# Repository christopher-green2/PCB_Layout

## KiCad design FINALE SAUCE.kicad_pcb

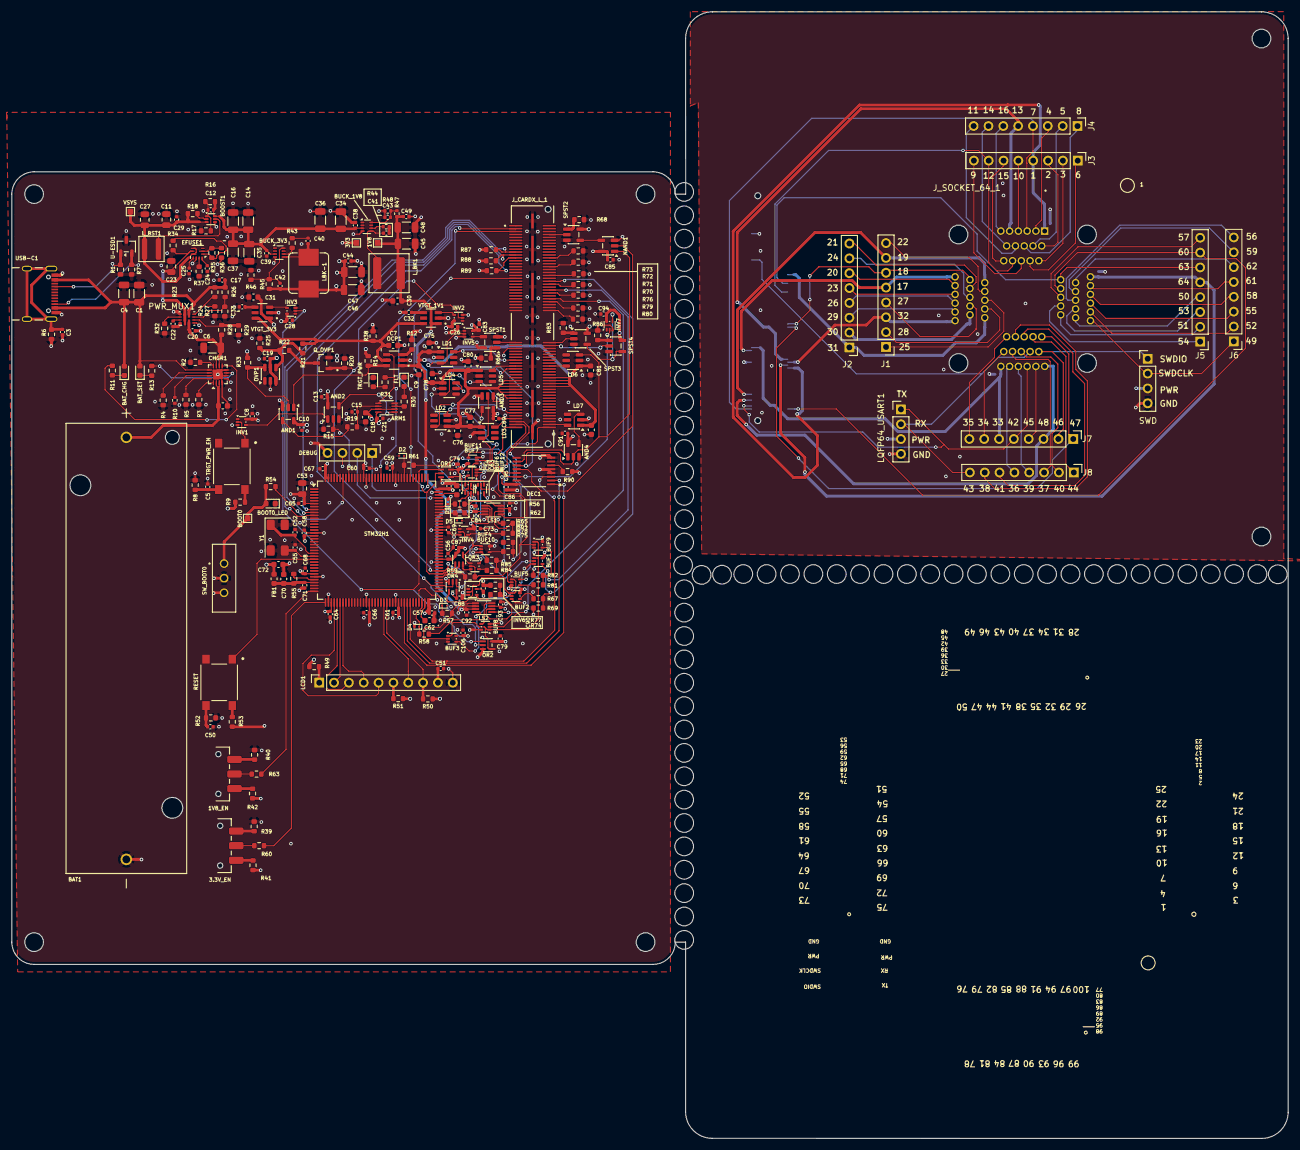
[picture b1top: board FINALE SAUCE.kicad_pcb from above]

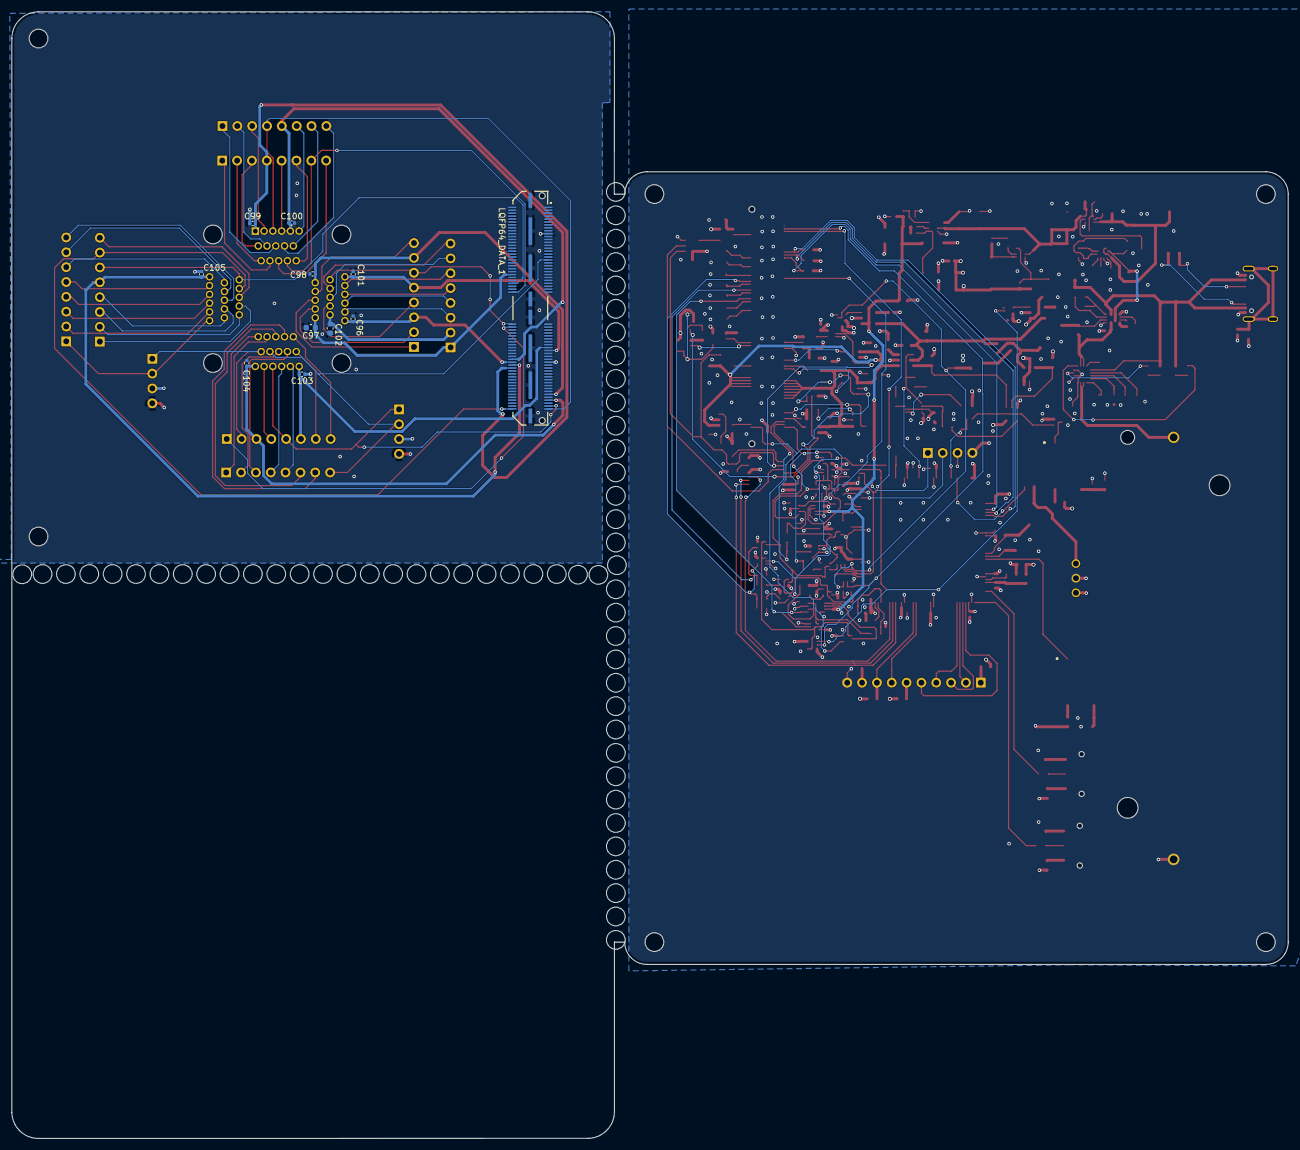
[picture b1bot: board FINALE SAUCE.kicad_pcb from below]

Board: 4 copper layers, 218.4 x 192.8 mm, 352 parts (11 on the bottom side), 236 nets.

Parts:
1V8, 3V3: TestPoint_Flag; TestPoint_Pad_1.0x1.0mm
1V8_EN, 3.3V_EN: JS102011SAQN; SW_SPDT_CK_JS102011SAQN
40, 41, 42, 43, 43#2, 44, 44#2, 45, 45#2, 46, 46#2, 47, 47#2, 48, 48#2, 49, 49#2, 50, 50#2, 51, 51#2, 52, 52#2, 53, 53#2, 54, 54#2, 55, 55#2, 56, 56#2, 57, 57#2, 58, 58#2, 59, 59#2, 60, 60#2, 61, 61#2, 62, 62#2, 63, 63#2, 64, 64#2, 65, 65#2, 66, 67, 68, 69, 70, 71, 72, 73, 74, 75: (no value)
AND1, AND2, AND3, AND4: SN74LVC1G08DBVT; SOT-23-5
ARM1: SN74LVC1G74DCUR; SOP50P310X90-8N
BAT1: 1043 Holder for 18650; BAT_1043
BAT_CHG: Green LED, V_f = 2.4 V at 20 mA, 0603; LED_0603_1608Metric
BAT_SET: Green LED, V_f = 2.4 V at 20 mA, 0603; LED_0603_1608Metric
BOOST1: TPS61023; SOT-563
BOOT0: TestPoint_Square; TestPoint_Pad_1.0x1.0mm
BOOT0_LED: LED; LED_0603_1608Metric
BUCK_1V8, BUCK_3V3: TPS62933P; SOT-583-8
BUF1, BUF2, BUF3, BUF4, BUF5, BUF6, BUF7, BUF8, BUF9, BUF10, BUF11, BUF12: 74AHC1G125; SOT-553
C1, C34, C35, C36: 10u; C_1206_3216Metric
C2: 4.7u; C_0603_1608Metric
C3, C39, C40, C44, C51, C54, C56, C57, C58, C59, C60, C61, C64, C65, C66, C67, C68, C69, C71, C92, C93, C95: 100nF; C_0402_1005Metric
C4, C46, C47: 22uF; C_1206_3216Metric
C5, C8, C26, C28, C50, C73, C74, C79, C83, C84, C85, C86, C87, C88, C89, C90, C91, C94, C106: .1uF; C_0402_1005Metric
C6, C14, C16, C45, C48: 22u; C_1206_3216Metric
C7, C9, C18, C30, C31: 1u; C_0603_1608Metric
C10, C13, C15, C17, C20, C21, C22, C29, C38, C41, C49: 100n; C_0402_1005Metric
C11, C23: 10u; C_0805_2012Metric
C12: 22p; C_0402_1005Metric
C19: 0.1u; C_0402_1005Metric
C24: 2.2n; C_0402_1005Metric
C25: 3.3n; C_0402_1005Metric
C27: 4.7u; C_0805_2012Metric
C32, C33: 1000pf; C_0402_1005Metric
C37: 10uF; C_1206_3216Metric
C42: 75pF; C_0402_1005Metric
C43: 10p; C_0402_1005Metric
C52, C55: 10pF; C_0402_1005Metric
C53: 4.7uF; C_0805_2012Metric
C62, C63: 2.2uF; C_0603_1608Metric
C70, C72, C75, C76, C77, C78, C80, C81, C82: 1uF; C_0603_1608Metric
C96, C98, C99, C100, C101, C103, C104, C105: .1u; C_0402_1005Metric
C97, C102: 2.2u; C_0603_1608Metric
CHGR1: BQ24074; VQFN-16-1EP_3x3mm_P0.5mm_EP1.6x1.6mm
D1, D2, D3, D4, D5: ESD9X5.0ST5G; D_SOD-923
DEC1: 74LCV138; TSSOP16B_TOS
EFUSE1: TPS259470L; Texas_RPU0010A_VQFN-HR-10_2x2mm_P0.5mm
FB1: 220; L_0603_1608Metric
FLT: Red LED, V_f ~ 2.0 V typ, 0603; LED_0603_1608Metric
INV1, INV2, INV3, INV4, INV5, INV6, INV7: 74LVC1GU04DRLR; SOT-553
J1, J2, J3, J4, J5, J6, J7, J8: Conn_01x08_Pin; PinHeader_1x08_P2.54mm_Vertical
J_CARDX_L_1: QSH-060-01-X-D-A; SAMTEC_QSH-060-01-X-D-A
J_SOCKET_64_1: IC51-0644-807; YAMAICHI_IC51-0644-807
LBK-1: 4.7u; L_Bourns_SRP7028A_7.3x6.6mm
LCD1: 358; PinSocket_1x10_P2.54mm_Vertical
LD1, LD2, LD3, LD4, LD5, LD6, LD7: TPS22917LDBVR; SOT-23-6
LQFP64_DATA_1: QTH-060-01-X-D-A; SAMTEC_QTH-060-01-X-D-A
LQFP64_USART1: Conn_01x04_Pin; PinHeader_1x04_P2.54mm_Vertical
LS1, LS2: TXS0102DCUR; VSSOP-8_2.3x2mm_P0.5mm
L_BK1: 6.8u WE-XHMI_6060; L_Wuerth_XHMI-6060
L_BST1: 1uH; L_Wuerth_MAPI-4030
NAND1: SN74LVC1G08DBVT; SOT-23-5
OCP1: MAX4995BAUT_T; SOT95P280X145-6N
OR1, OR2, OR3, OR4: 74AHC1G32QSE-7; SOT-353_SC-70-5
OVP1: TPS3700DDCR; SOT-23-6
PWR_MUX1: TPS2121RUXR; RUX0012A
Q_OVP1: 2N7002
R1, R7: 5.1k; R_0603_1608Metric
R2: 1.18k; R_0603_1608Metric
R3, R8, R9, R14, R19, R38, R39, R40, R41, R42, R46, R50, R51, R52, R53, R54, R64, R66, R67, R68, R70, R71, R72, R73, R74, R75, R76, R79, R80, R81, R83, R84, R86, R90: 10k; R_0603_1608Metric
R4: 46.4k; R_0603_1608Metric
R5: 1.13k; R_0603_1608Metric
R6, R21: 1M; R_0603_1608Metric
R10: 4.12k; R_0402_1005Metric
R11, R13: 330; R_0603_1608Metric
R12: 94.2k; R_0603_1608Metric
R15, R17, R18, R20, R33, R87, R88, R89: 100k; R_0603_1608Metric
R16: 732k; R_0603_1608Metric
R22: 249k; R_0603_1608Metric
R23: 10.2k; R_0603_1608Metric
R24, R27, R29: 5k; R_0603_1608Metric
R25: 258k; R_0603_1608Metric
R26: 21k; R_0603_1608Metric
R28: 18.6k; R_0603_1608Metric
R30: 680; R_0603_1608Metric
R31: 470; R_0603_1608Metric
R32: 44.2k; R_0603_1608Metric
R34: 470k; R_0603_1608Metric
R35: 66.5k; R_0603_1608Metric
R36: 133k; R_0603_1608Metric
R37: 1.10k; R_0603_1608Metric
R43: 3.3; R_0603_1608Metric
R44: 3.3; R_0402_1005Metric
R45: 31.25k; R_0603_1608Metric
R47: 12.5k; R_0402_1005Metric
R48: 10k; R_0402_1005Metric
R49: 220; R_0603_1608Metric
R55: 47; R_0603_1608Metric
R56, R57, R58, R62: 22; R_0603_1608Metric
R59, R60, R61, R63: 100; R_0603_1608Metric
R65, R69, R77, R78, R82, R85: 12k; R_0603_1608Metric
RESET: PTS645; SWITCH_43SMTR92LFS
SPST1, SPST2, SPST3, SPST4: TS5A3166DBVR; SOT-23-5
STM32H1: STM32H753ZIT6; LQFP-144_20x20mm_P0.5mm
SWD: Conn_01x04_Pin; PinHeader_1x04_P2.54mm_Vertical
SW_BOOT0: EG1218; SW_EG1218
TRGT_PWR: Green LED, V_f = 2.4 V at 20 mA, 0603; LED_0603_1608Metric
TRGT_PWR_EN: PTS645; SWITCH_43SMTR92LFS
U-ESD1: TPD2E009DRTR; SOT-23-3
USB-C1: USB4105-GF-A; GCT_USB4105-GF-A
VSYS: TestPoint_Flag; TestPoint_Pad_1.0x1.0mm
VTGT_1V1, VTGT_3V3: TPS22918DBVR; SOT95P280X145-6N
Y1: Crystal_GND24; Crystal_SMD_0603-4Pin_6.0x3.5mm
cg-SWD_Breakout_Parent1: Conn_01x04_Pin; PinHeader_1x04_P2.54mm_Vertical

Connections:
1V8: 1V8.1 (1_1), C30.1, C45.1, C48.1, C49.1, C84.1, C92.1, LS1.3 (VCCA), LS2.3 (VCCA), L_BK1.2, R47.1, VTGT_1V1.1 (VIN)
1V8_ENABLE: INV2.2, OR3.1, OR4.1, Q_OVP1.1, R20.1, STM32H1.80 (PD11)
3V3: 3V3.1 (1_1), AND1.5 (VCC), AND2.5 (VCC), AND3.5 (VCC), AND4.5 (VCC), ARM1.2 (D), ARM1.7 (~PRE), ARM1.8 (VCC), BUF1.5 (VCC), BUF2.5 (VCC), BUF3.5 (VCC), BUF4.5 (VCC), BUF5.5 (VCC), BUF6.5 (VCC), BUF7.5 (VCC), BUF8.5 (VCC), BUF9.5 (VCC), BUF10.5 (VCC), BUF11.5 (VCC), BUF12.5 (VCC), C8.1, C10.1, C13.2, C18.1, C19.1, C21.1, C26.1, C28.1, C31.1, C42.1, C44.1, C46.1, C47.1, C51.1, C53.1, C54.1, C56.1, C57.1, C58.1, C59.1, C60.1, C61.1, C64.1, C65.1, C66.1, C67.1, C68.1, C72.1, C73.1, C74.1, C79.1, C83.1, C85.1, C86.1, C87.1, C88.1, C89.1, C90.1, C91.1, C93.1, C94.1, C95.1, C106.1, CHGR1.5 (EN2), DEC1.16 (VCC), FB1.1, INV1.5 (VCC), INV2.5 (VCC), INV3.5 (VCC), INV4.5 (VCC), INV5.5 (VCC), INV6.5 (VCC), INV7.5 (VCC), J_CARDX_L_1.65, LBK-1.2, LCD1.9 (VCC), LS1.7 (VCCB), LS2.7 (VCCB), NAND1.5 (VCC), OR1.5 (VCC), OR2.5 (VCC), OR3.5 (VCC), OR4.5 (VCC), OVP1.3 (INA+), OVP1.5 (VDD), R9.2, R14.1, R33.1, R41.1, R42.2, R45.1, R49.1, R50.1, R51.1, R53.2, R87.1, R88.1, R89.1, R90.1, SPST1.5 (V+), SPST2.5 (V+), SPST3.5 (V+), SPST4.5 (V+), STM32H1.6 (VBAT), STM32H1.17 (VDD), STM32H1.30 (VDD), STM32H1.39 (VDD), STM32H1.52 (VDD), STM32H1.62 (VDD), STM32H1.72 (VDD), STM32H1.84 (VDD), STM32H1.108 (VDD), STM32H1.121 (VDD), STM32H1.131 (VDD), STM32H1.143 (PDR_ON), STM32H1.144 (VDD), SW_BOOT0.3, VTGT_3V3.1 (VIN), cg-SWD_Breakout_Parent1.3
3V3_ENABLE: INV3.2, OR1.1, OR2.1, STM32H1.112 (PC11)
5V: BOOST1.6 (VOUT), BUCK_1V8.3 (VIN), BUCK_3V3.3 (VIN), C12.1, C14.1, C16.1, C34.1, C35.1, C36.1, C37.1, C38.1, C39.1, R16.1
/Parent_MCU/HSE_IN: C52.1, STM32H1.23 (PH0), Y1.1
/Parent_MCU/HSE_OUT: C55.1, STM32H1.24 (PH1), Y1.3
/Parent_MCU/LCD_DATA/COMMAND: LCD1.7 (D/C), STM32H1.57 (PG1)
/Parent_MCU/LCD_NRST: LCD1.8 (RESET), R50.2, STM32H1.58 (PE7)
/Parent_MCU/SPI_MISO: LCD1.2 (MISO), STM32H1.42 (PA6)
/Parent_MCU/SPI_MOSI: LCD1.4 (MOSI), STM32H1.43 (PA7)
/Parent_MCU/SPI_NSS: LCD1.5 (TFT_CS), STM32H1.40 (PA4)
/Parent_MCU/SPI_SCK: LCD1.3 (SCK), STM32H1.41 (PA5)
/Parent_MCU/SWDCLK: STM32H1.105 (PA13), cg-SWD_Breakout_Parent1.2
/Parent_MCU/SWDIO: STM32H1.109 (PA14), cg-SWD_Breakout_Parent1.1
/Parent_MCU/VDDA: C70.1, C71.1, FB1.2, R55.1, STM32H1.33 (VDDA)
/PowerSupply/EFUSE_DVDT: C25.1, EFUSE1.7 (dVdt)
/PowerSupply/ILIM_NODE: CHGR1.12 (ILIM), R2.2
/PowerSupply/ISET_NODE: CHGR1.16 (ISET), R5.2
/PowerSupply/TMR_NODE: CHGR1.14 (TMR), R4.2
/PowerSupply/USB_CC1: R1.2, U-ESD1.1 (D+), USB-C1.A5 (CC1)
/PowerSupply/USB_CC2: R7.2, U-ESD1.2 (D-), USB-C1.B5 (CC2)
/PowerSupply/VSYS_ILM: PWR_MUX1.10 (ILIM), R32.2
/PowerSupply/VSYS_OV1: PWR_MUX1.5 (OV1), R26.1, R27.2
/PowerSupply/VSYS_OV2: PWR_MUX1.4 (OV2), R28.1, R29.2
/PowerSupply/VSYS_PR1: PWR_MUX1.6 (PR1), R23.1, R24.2
/PowerSupply/VSYS_SS: C22.1, PWR_MUX1.11 (SS)
/Profile_Switching/64_1: C99.1, J3.4, J_SOCKET_64_1.1, LQFP64_DATA_1.92
/Profile_Switching/64_2: J3.3, J_SOCKET_64_1.2
/Profile_Switching/64_3: J3.2, J_SOCKET_64_1.3
/Profile_Switching/64_4: J4.3, J_SOCKET_64_1.4
/Profile_Switching/64_5: J4.2, J_SOCKET_64_1.5
/Profile_Switching/64_6: J3.1, J_SOCKET_64_1.6
/Profile_Switching/64_7: J4.4, J_SOCKET_64_1.7, LQFP64_DATA_1.119
/Profile_Switching/64_8: J4.1, J_SOCKET_64_1.8
/Profile_Switching/64_9: J3.8, J_SOCKET_64_1.9
/Profile_Switching/64_10: J3.5, J_SOCKET_64_1.10
/Profile_Switching/64_11: J4.8, J_SOCKET_64_1.11
/Profile_Switching/64_12: J3.7, J_SOCKET_64_1.12, LQFP64_DATA_1.60
/Profile_Switching/64_13: C100.1, J4.5, J_SOCKET_64_1.13, LQFP64_DATA_1.86
/Profile_Switching/64_14: J4.7, J_SOCKET_64_1.14
/Profile_Switching/64_15: J3.6, J_SOCKET_64_1.15
/Profile_Switching/64_16: J4.6, J_SOCKET_64_1.16
/Profile_Switching/64_17: C101.1, J1.5, J_SOCKET_64_1.17, LQFP64_DATA_1.79
/Profile_Switching/64_18: J1.6, J_SOCKET_64_1.18, LQFP64_DATA_1.62
/Profile_Switching/64_19: C98.1, J1.7, J_SOCKET_64_1.19, LQFP64_DATA_1.109
/Profile_Switching/64_20: J2.6, J_SOCKET_64_1.20
/Profile_Switching/64_21: J2.8, J_SOCKET_64_1.21
/Profile_Switching/64_22: J1.8, J_SOCKET_64_1.22
/Profile_Switching/64_23: J2.5, J_SOCKET_64_1.23
/Profile_Switching/64_24: J2.7, J_SOCKET_64_1.24
/Profile_Switching/64_25: J1.1, J_SOCKET_64_1.25
/Profile_Switching/64_26: J2.4, J_SOCKET_64_1.26
/Profile_Switching/64_27: J1.4, J_SOCKET_64_1.27
/Profile_Switching/64_28: J1.2, J_SOCKET_64_1.28
/Profile_Switching/64_29: J2.3, J_SOCKET_64_1.29
/Profile_Switching/64_30: C102.1, J2.2, J_SOCKET_64_1.30
/Profile_Switching/64_31: C97.1, J2.1, J_SOCKET_64_1.31, LQFP64_DATA_1.48
/Profile_Switching/64_32: C96.1, J1.3, J_SOCKET_64_1.32, LQFP64_DATA_1.88
/Profile_Switching/64_33: C103.1, J7.6, J_SOCKET_64_1.33, LQFP64_DATA_1.77
/Profile_Switching/64_34: J7.7, J_SOCKET_64_1.34
/Profile_Switching/64_35: J7.8, J_SOCKET_64_1.35
/Profile_Switching/64_36: J8.5, J_SOCKET_64_1.36
/Profile_Switching/64_37: J8.3, J_SOCKET_64_1.37
/Profile_Switching/64_38: J8.7, J_SOCKET_64_1.38
/Profile_Switching/64_39: J8.4, J_SOCKET_64_1.39
/Profile_Switching/64_40: J8.2, J_SOCKET_64_1.40
/Profile_Switching/64_41: J8.6, J_SOCKET_64_1.41
/Profile_Switching/64_42: J7.5, J_SOCKET_64_1.42, LQFP64_DATA_1.117, LQFP64_USART1.1
/Profile_Switching/64_43: J8.8, J_SOCKET_64_1.43, LQFP64_DATA_1.37, LQFP64_USART1.2
/Profile_Switching/64_44: J8.1, J_SOCKET_64_1.44
/Profile_Switching/64_45: J7.4, J_SOCKET_64_1.45
/Profile_Switching/64_46: J7.2, J_SOCKET_64_1.46, SWD.1
/Profile_Switching/64_47: J7.1, J_SOCKET_64_1.47, LQFP64_DATA_1.64
/Profile_Switching/64_48: C104.2, J7.3, J_SOCKET_64_1.48, LQFP64_DATA_1.113
/Profile_Switching/64_49: J6.1, J_SOCKET_64_1.49, SWD.2
/Profile_Switching/64_50: J5.4, J_SOCKET_64_1.50
/Profile_Switching/64_51: J5.2, J_SOCKET_64_1.51
/Profile_Switching/64_52: J6.2, J_SOCKET_64_1.52
/Profile_Switching/64_53: J5.3, J_SOCKET_64_1.53
/Profile_Switching/64_54: J5.1, J_SOCKET_64_1.54
/Profile_Switching/64_55: J6.3, J_SOCKET_64_1.55
/Profile_Switching/64_56: J6.8, J_SOCKET_64_1.56
/Profile_Switching/64_57: J5.8, J_SOCKET_64_1.57
/Profile_Switching/64_58: J6.4, J_SOCKET_64_1.58
/Profile_Switching/64_59: J6.7, J_SOCKET_64_1.59
/Profile_Switching/64_60: J5.7, J_SOCKET_64_1.60, LQFP64_DATA_1.120
/Profile_Switching/64_61: J6.5, J_SOCKET_64_1.61
/Profile_Switching/64_62: J6.6, J_SOCKET_64_1.62
/Profile_Switching/64_63: J5.6, J_SOCKET_64_1.63, LQFP64_DATA_1.54
/Profile_Switching/64_64: C105.1, J5.5, J_SOCKET_64_1.64, LQFP64_DATA_1.90
/Profile_Switching/LQFP64_PIN_7: BUF11.4, J_CARDX_L_1.119, R84.2, R85.1
/Profile_Switching/LQFP64_PIN_12: J_CARDX_L_1.60, R80.2
/Profile_Switching/LQFP64_PIN_17: J_CARDX_L_1.79, LD4.6 (VOUT)
/Profile_Switching/LQFP64_PIN_18: J_CARDX_L_1.62, SPST3.2
/Profile_Switching/LQFP64_PIN_19: J_CARDX_L_1.109, LD2.6 (VOUT)
/Profile_Switching/LQFP64_PIN_31: J_CARDX_L_1.48, R76.2
/Profile_Switching/LQFP64_PIN_33: J_CARDX_L_1.77, LD5.6 (VOUT)
/Profile_Switching/LQFP64_PIN_42: BUF12.2, J_CARDX_L_1.117, LS1.5 (A1)
/Profile_Switching/LQFP64_PIN_43: BUF6.4, J_CARDX_L_1.37, LS1.4 (A2)
/Profile_Switching/LQFP64_PIN_47: J_CARDX_L_1.64, SPST4.2
/Profile_Switching/LQFP64_PIN_48: J_CARDX_L_1.113, LD3.6 (VOUT)
/Profile_Switching/LQFP64_PIN_60: BUF7.4, J_CARDX_L_1.120, R75.2, R78.1
/Profile_Switching/LQFP64_PIN_63: J_CARDX_L_1.54, R79.2
/Profile_Switching/LQFP100_PIN_10: J_CARDX_L_1.61, SPST1.2
/Profile_Switching/LQFP100_PIN_11: J_CARDX_L_1.78, LD6.6 (VOUT)
/Profile_Switching/LQFP100_PIN_14: BUF9.4, J_CARDX_L_1.46, R81.2, R82.1
/Profile_Switching/LQFP100_PIN_19: J_CARDX_L_1.73, LD1.6 (VOUT)
/Profile_Switching/LQFP100_PIN_20: J_CARDX_L_1.24, R73.2
/Profile_Switching/LQFP100_PIN_22: J_CARDX_L_1.118, LD7.6 (VOUT)
/Profile_Switching/LQFP100_PIN_27: J_CARDX_L_1.08, SPST2.2
/Profile_Switching/LQFP100_PIN_49: J_CARDX_L_1.30, R72.2
/Profile_Switching/LQFP100_PIN_68: BUF8.2, J_CARDX_L_1.52, LS2.5 (A1)
/Profile_Switching/LQFP100_PIN_69: BUF3.4, J_CARDX_L_1.115, LS2.4 (A2)
/Profile_Switching/LQFP100_PIN_74: J_CARDX_L_1.36, R71.2
/Profile_Switching/LQFP100_PIN_94: BUF1.4, J_CARDX_L_1.40, R67.2, R69.1
/Profile_Switching/LQFP100_PIN_99: J_CARDX_L_1.42, R70.2
/Profile_Switching/TGT_PWR64: LQFP64_DATA_1.87, LQFP64_USART1.3, SWD.3
CARD_ID0_N: J_CARDX_L_1.19, R87.2, STM32H1.10 (PF0)
CARD_ID1_N: J_CARDX_L_1.21, R88.2, STM32H1.9 (PC15)
CARD_ID2_N: J_CARDX_L_1.23, R89.2, STM32H1.8 (PC14)
GND: AND1.3 (GND), AND2.3 (GND), AND3.3 (GND), AND4.3 (GND), ARM1.4 (GND), BAT1.N, BOOST1.4 (GND), BOOT0_LED.1 (K), BUCK_1V8.4 (GND), BUCK_3V3.4 (GND), BUF1.3 (GND), BUF2.3 (GND), BUF3.3 (GND), BUF4.3 (GND), BUF5.3 (GND), BUF6.3 (GND), BUF7.3 (GND), BUF8.3 (GND), BUF9.3 (GND), BUF10.3 (GND), BUF11.3 (GND), BUF12.3 (GND), C1.2, C2.2, C3.2, C4.2, C5.2, C6.2, C7.2, C8.2, C9.2, C10.2, C11.2, C13.1, C14.2, C15.2, C16.2, C17.2, C18.2, C19.2, C20.2, C21.2, C22.2, C23.2, C24.2, C25.2, C26.2, C27.2, C28.2, C29.2, C30.2, C31.2, C32.2, C33.2, C34.2, C35.2, C36.2, C37.2, C38.2, C39.2, C43.2, C44.2, C45.2, C46.2, C47.2, C48.2, C49.2, C50.2, C51.2, C52.2, C53.2, C54.2, C55.2, C56.2, C57.2, C58.2, C59.2, C60.2, C61.2, C62.2, C63.2, C64.2, C65.2, C66.2, C67.2, C68.2, C69.2, C70.2, C71.2, C72.2, C73.2, C74.2, C75.2, C76.2, C77.2, C78.2, C79.2, C80.2, C81.2, C82.2, C83.2, C84.2, C85.2, C86.2, C87.2, C88.2, C89.2, C90.2, C91.2, C92.2, C93.2, C94.2, C95.2, C106.2, CHGR1.4 (~CE), CHGR1.6 (EN1), CHGR1.8 (VSS), CHGR1.17 (EXP), D1.2 (A), D2.2 (A), D3.2 (A), D4.2 (A), D5.2 (A), DEC1.4 (*G2A), DEC1.5 (*G2B), DEC1.8 (GND), EFUSE1.8 (GND), FLT.1 (K), INV1.3 (GND), INV2.3 (GND), INV3.3 (GND), INV4.3 (GND), INV5.3 (GND), INV6.3 (GND), INV7.3 (GND), J_CARDX_L_1.G1_1 (GND1), J_CARDX_L_1.G1_2 (GND1__1), J_CARDX_L_1.G1_3 (GND1__2), J_CARDX_L_1.G1_4 (GND1__3), J_CARDX_L_1.G2_1 (GND2), J_CARDX_L_1.G2_2 (GND2__1), J_CARDX_L_1.G2_3 (GND2__2), J_CARDX_L_1.G2_4 (GND2__3), LCD1.10 (GND), LD1.2 (GND), LD2.2 (GND), LD3.2 (GND), LD4.2 (GND), LD5.2 (GND), LD6.2 (GND), LD7.2 (GND), LS1.2 (GND), LS2.2 (GND), NAND1.3 (GND), OCP1.2 (GND), OR1.3 (GND), OR2.3 (GND), OR3.3 (GND), OR4.3 (GND), OVP1.2 (GND), PWR_MUX1.3 (CP2), PWR_MUX1.9 (ST), PWR_MUX1.12 (GND), Q_OVP1.2, R1.1, R2.1, R3.1, R4.1, R5.1, R6.1, R7.1, R8.2, R10.1, R12.2, R15.2, R17.2, R20.2, R24.1, R25.2, R27.1, R29.1, R32.1, R36.1, R37.1, R38.2, R39.2, R40.2, R46.2, R48.2, R52.2, R65.1, R66.2, R68.2, R69.2, R70.1, R71.1, R72.1, R73.1, R76.1, R77.1, R78.2, R79.1, R80.1, R82.2, R83.2, R85.2, R86.2, SPST1.3 (GND), SPST2.3 (GND), SPST3.3 (GND), SPST4.3 (GND), STM32H1.16 (VSS), STM32H1.31 (VSSA), STM32H1.38 (VSS), STM32H1.51 (VSS), STM32H1.61 (VSS), STM32H1.83 (VSS), STM32H1.94 (VSS), STM32H1.107 (VSS), STM32H1.120 (VSS), STM32H1.130 (VSS), SW_BOOT0.2, TRGT_PWR.1 (K), U-ESD1.3 (GND), USB-C1.A1_B12 (GND), USB-C1.B1_A12 (GND__1), VTGT_1V1.2 (GND), VTGT_3V3.2 (GND), Y1.2 (G), Y1.4 (G), cg-SWD_Breakout_Parent1.4
GND64: C96.2, C97.2, C98.2, C99.2, C100.2, C101.2, C102.2, C103.2, C104.1, C105.2, LQFP64_DATA_1.19, LQFP64_DATA_1.G1 (GND), LQFP64_DATA_1.G2 (GND__1), LQFP64_DATA_1.G3 (GND__2), LQFP64_DATA_1.G4 (GND__3), LQFP64_DATA_1.G5 (GND__4), LQFP64_DATA_1.G6 (GND__5), LQFP64_DATA_1.G7 (GND__6), LQFP64_DATA_1.G8 (GND__7), LQFP64_USART1.4, SWD.4
LQFP64_1V8_ENABLE: BUF4.1, BUF10.1, INV4.2, OR3.4
LQFP64_3V3_ENABLE: BUF6.1, BUF7.1, BUF11.1, BUF12.1, OR1.4
LQFP64_ENABLE: J_CARDX_L_1.05, OR1.2, OR3.2, STM32H1.79 (PD10)
LQFP100_1V8_ENABLE: BUF2.1, BUF5.1, INV6.2, OR4.4
LQFP100_3V3_ENABLE: BUF1.1, BUF3.1, BUF8.1, BUF9.1, OR2.4
LQFP100_ENABLE: J_CARDX_L_1.03, OR2.2, OR4.2, STM32H1.75 (PB14)
MCU_1V8_FLAG: 1V8_EN.2, R63.2
MCU_3V3_FLAG: 3.3V_EN.2, R60.2
MCU_PROFILE_SEL1: DEC1.1 (A), STM32H1.64 (PE11)
MCU_PROFILE_SEL2: DEC1.2 (B), STM32H1.65 (PE12)
MCU_PROFILE_SEL3: DEC1.3 (C), STM32H1.66 (PE13)
MCU_TARGET_PROFILE_ENABLE: AND2.2 (B), R15.1, STM32H1.136 (PB6)
unnamed: 1V8_EN.1, R40.1
unnamed: 1V8_EN.3, R42.1
unnamed: 3.3V_EN.1, R39.1
unnamed: 3.3V_EN.3, R41.2
unnamed: AND1.4 (Y), R19.1
unnamed: AND2.4 (Y), ARM1.1 (CLK)
unnamed: ARM1.6 (~CLR), C15.1, R19.2
unnamed: ARM1.3 (~Q), R30.1
unnamed: BAT_CHG.1 (K), R11.1
unnamed: BAT_SET.1 (K), R13.1
unnamed: BOOST1.2 (EN), R18.2
unnamed: BOOST1.1 (FB), C12.2, R16.2, R17.1
unnamed: BOOST1.5 (SW), L_BST1.2
unnamed: BOOT0.1 (1_1), BOOT0_LED.2 (A), R54.1, SW_BOOT0.1
unnamed: BUCK_1V8.6 (BST), R44.1
unnamed: BUCK_1V8.8 (FB), C43.1, R47.2, R48.1
unnamed: BUCK_1V8.5 (SW), C41.2, L_BK1.1
unnamed: BUCK_3V3.6 (BST), R43.1
unnamed: BUCK_3V3.8 (FB), C42.2, R45.2, R46.1
unnamed: BUCK_3V3.5 (SW), C40.2, LBK-1.1
unnamed: BUF2.4, R67.1
unnamed: BUF4.4, R75.1
unnamed: BUF5.4, R81.1
unnamed: BUF10.4, R84.1
unnamed: C5.1, R8.1, TRGT_PWR_EN.4
unnamed: C40.1, R43.2
unnamed: C41.1, R44.2
unnamed: C50.1, R52.1, RESET.4
unnamed: C62.1, STM32H1.71 (VCAP)
unnamed: C63.1, STM32H1.106 (VCAP)
unnamed: BAT1.P, C2.1, CHGR1.2 (BAT_2), CHGR1.3 (BAT_3)
unnamed: CHGR1.15 (ITERM), R10.2
unnamed: CHGR1.1 (TS), R3.2
unnamed: CHGR1.9 (~CHG), R11.2
unnamed: CHGR1.7 (~PGOOD), R13.2
unnamed: D1.1 (K), R56.1, STM32H1.102 (PA10)
unnamed: D2.1 (K), R61.1, STM32H1.117 (PD3)
unnamed: D3.1 (K), R57.1, STM32H1.69 (PB10)
unnamed: D4.1 (K), R58.1, STM32H1.70 (PB11)
unnamed: D5.1 (K), R62.1, STM32H1.101 (PA9)
unnamed: DEC1.6 (G1), R90.2
unnamed: EFUSE1.1 (EN_UVLO), R34.1, R35.2
unnamed: EFUSE1.9 (ILM), R37.2
unnamed: C23.1, EFUSE1.5 (IN), PWR_MUX1.1 (OUT), PWR_MUX1.8 (OUT__2), R34.2
unnamed: C24.1, EFUSE1.10 (ITIMER)
unnamed: EFUSE1.2 (OVCSEL), R35.1, R36.2
unnamed: FLT.2 (A), R30.2
unnamed: INV1.2, TRGT_PWR_EN.1
unnamed: INV4.4, R64.1
unnamed: INV5.4, SPST1.4
unnamed: INV6.4, R74.1
unnamed: INV7.4, SPST3.4, SPST4.4
unnamed: LCD1.6 (CARD_CS), R51.2
unnamed: LCD1.1 (LITE), R49.2
unnamed: AND3.4, LD2.3 (~ON)
unnamed: AND4.4, LD7.3 (~ON)
unnamed: LS1.6 (OE), R64.2, R65.2
unnamed: LS2.6 (OE), R74.2, R77.2
unnamed: NAND1.4, SPST2.4
unnamed: OCP1.3 (SETI), R12.1
unnamed: OVP1.4 (INB-), R21.2, R22.1, R25.1
unnamed: Q_OVP1.3, R22.2
unnamed: R9.1, TRGT_PWR_EN.2
unnamed: R53.1, RESET.2
unnamed: R66.1, SPST1.1
unnamed: R68.1, SPST2.1
unnamed: R83.1, SPST3.1
unnamed: R86.1, SPST4.1
unnamed: R54.2, STM32H1.138 (BOOT0)
unnamed: RESET.1, STM32H1.25 (NRST)
unnamed: R63.1, STM32H1.36 (PA2)
unnamed: R60.1, STM32H1.37 (PA3)
unnamed: R59.1, STM32H1.78 (PD9)
unnamed: C69.1, STM32H1.95 (VDD33_USB)
unnamed: R55.2, STM32H1.32 (VREF+)
unnamed: R31.2, TRGT_PWR.2 (A)
unnamed: C3.1, R6.2, USB-C1.SH1 (SHELL_GND), USB-C1.SH2 (SHELL_GND__1), USB-C1.SH3 (SHELL_GND__2), USB-C1.SH4 (SHELL_GND__3)
unnamed: C32.1, VTGT_1V1.4 (CT)
unnamed: INV2.4, VTGT_1V1.3 (ON)
unnamed: C33.1, VTGT_3V3.4 (CT)
unnamed: INV3.4, VTGT_3V3.3 (ON)
OCP_FLT_N: AND1.1 (A), OCP1.6 (~FLAG), R14.2
OVP_FLT_N: AND1.2 (B), OVP1.6 (OUTB), R33.2
SYS_OUT: C6.1, C20.1, CHGR1.10 (OUT_10), CHGR1.11 (OUT_11), PWR_MUX1.2 (IN2), R28.2
TARGET_BOOT0_CONTROL: BUF1.2, BUF2.2, BUF4.2, BUF7.2, R61.2
TARGET_POWER_RAIL: C7.1, OCP1.5 (IN), R21.1, R38.1, VTGT_1V1.6 (VOUT), VTGT_3V3.6 (VOUT)
TARGET_POWER_SUPPLY: C9.1, C75.1, C76.1, C77.1, C78.1, C80.1, C81.1, C82.1, J_CARDX_L_1.86, J_CARDX_L_1.87, J_CARDX_L_1.88, J_CARDX_L_1.89, J_CARDX_L_1.90, J_CARDX_L_1.91, J_CARDX_L_1.92, J_CARDX_L_1.93, J_CARDX_L_1.95, J_CARDX_L_1.97, J_CARDX_L_1.99, LD1.1 (VIN), LD2.1 (VIN), LD3.1 (VIN), LD4.1 (VIN), LD5.1 (VIN), LD6.1 (VIN), LD7.1 (VIN), OCP1.1 (OUT)
TARGET_PROFILE_1: AND3.2, DEC1.14 (*Y1), INV7.2, LD3.3 (~ON)
TARGET_PROFILE_2: AND3.1, DEC1.13 (*Y2), LD4.3 (~ON), LD5.3 (~ON)
TARGET_PROFILE_3: DEC1.12 (*Y3), NAND1.2
TARGET_PROFILE_4: AND4.2, DEC1.11 (*Y4), INV5.2, LD1.3 (~ON), LD6.3 (~ON), NAND1.1
TARGET_PROFILE_5: AND4.1, DEC1.10 (*Y5)
TARGET_PWR_ENABLE: ARM1.5 (Q), OCP1.4 (ON), R31.1, STM32H1.125 (PG10)
TARGET_PWR_ENABLE_BUTTON: AND2.1 (A), INV1.4
TARGET_RESET_CONTROL: BUF5.2, BUF9.2, BUF10.2, BUF11.2, R59.2
USART1_RX: BUF12.4, LS1.8 (B1), R56.2
USART1_TX: BUF6.2, LS1.1 (B2), R62.2
USART3_RX: BUF8.4, LS2.8 (B1), R58.2
USART3_TX: BUF3.2, LS2.1 (B2), R57.2
USB_VBUS: BAT_CHG.2 (A), BAT_SET.2 (A), C1.1, C4.1, C17.1, CHGR1.13 (IN), PWR_MUX1.7 (IN1), R23.2, R26.2, USB-C1.A4_B9 (VBUS), USB-C1.B4_A9 (VBUS__1)
V_SYS: BOOST1.3 (VIN), C11.1, C27.1, C29.1, EFUSE1.4 (PGTH), EFUSE1.6 (OUT), L_BST1.1, R18.1, VSYS.1 (1_1)
